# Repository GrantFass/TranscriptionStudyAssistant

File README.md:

# 24-Transcription-Study-Assistant

## Description
This project aims to create a tool that will assist in taking transcripts of courses and
breaking them down into pieces that can more easily be used for studying. This tool is 
intended to be utilized by all audiences but may be particularly beneficial for
neurodivergent students that face sensory overload during long lectures. 

This project is divided into three primary components.
1. Hardware
2. Web Software
3. Machine Learning

The hardware team is focusing on developing a video taking device for use with Microsoft
Teams, and other meeting software. This is meant to be an alternative to the [Meeting Owl 3](https://owllabs.com/products/meeting-owl-3?utm_source=adwords&utm_campaign=US_Branded&utm_medium=ppc&utm_term=meeting%20owl%203&hsa_kw=meeting%20owl%203&hsa_mt=e&hsa_tgt=kwd-1664191677785&hsa_src=g&hsa_ad=617179448370&hsa_ver=3&hsa_cam=1485487619&hsa_net=adwords&hsa_acc=2493962266&hsa_grp=78790216762&gclid=Cj0KCQiA_bieBhDSARIsADU4zLcaWRQWOvktF4fADjmooEcVXLYf4rbGnzq8EmovNgqnJcjop1JarCsaAsLBEALw_wcB).
The primary benefit that our device has over the meeting owl is cost. Our device aims to be
manufacturable as a proof of concept for under $200. This is much cheaper than the $1050
price tag the Meeting Owl 3 costs. Our device is meant to be an assistant for tracking
presenters in a classroom like environment for meetings.

The software team is focusing on developing a website that will support all the necessary
functions of our application, including our machine learning models. The website will be
designed so that video transcripts and other text based files can be uploaded to the server.
Then the server will allow you to modify and clean up the text, generate summaries of the
content, identify relevant topics, and possibly build study aids. An example study aid would
be question and answer flashcards.

The machine learning team is focusing on the models that allow us to summarize text and topics.
This is primarily done through transformers and Latent Dirichlet Allocation models.

## Badges
On some READMEs, you may see small images that convey metadata, such as whether or not all the tests are passing for the project. You can use Shields to add some to your README. Many services also have instructions for adding a badge.

## Visuals
Depending on what you are making, it can be a good idea to include screenshots or even a video (you'll frequently see GIFs rather than actual videos). Tools like ttygif can help, but check out Asciinema for a more sophisticated method.

## Automatic Installation
Running this project locally can be done through a few simple steps. 
The first step is to install `python 3.10.0`. Once that is done,
you should be able to install the project by running setup.py. Once this is
completed you can run the entire project through run.py

## Manual Installation
Running this project locally can be somewhat difficult as there are external requirements.
Assuming that the proper python version (as noted in the requirements section) is installed
it should be possible to install relevant python library files by running the command
`pip install -r requirements.txt` out of the software home directory.

This application uses the SpaCy library and its language kits. Unfortunately, these can not be
installed through pip. Instead, they must be installed through the command line.
There are three model sizes that must be installed to be able to run the software. These
models can be found from [SpaCy](https://spacy.io/models/en). Download using the following commands:
- `python -m spacy download en_core_web_sm`
- `python -m spacy download en_core_web_md`
- `python -m spacy download en_core_web_lg`

The SpaCy `en_core_web_trf` model is not required.

The step is installing MinIO. MinIO is an object store that can be downloaded [here](https://min.io/download#/windows).
Both the server, and the client, must be downloaded. If on Windows, this will give two files:
`minio.exe` and `mc.exe`. Place these two executeables in a folder that you can run things from.
In order to run the web backend you must launch a console out of the folder and run the command:
`minio server minio_data`. This starts the object store which allows for storing log files as
well as files that are uploaded to the program.

The next step is to set up users and buckets inside MinIO. Access the [MinIO web interface](http://127.0.0.1:9000/).
Log in with the default username `minioadmin` and default password `minioadmin`.
Next you should see a sidebar of options. Click on Administrator -> Identity -> Users ->
Create User. You should then create a user called `tsa-backend`. Give it a password you can
remember as well as read write access then save. Next navigate to Administrator -> Buckets.
We need to create a bucket called `tsa-backend-endpoint-logs` and another bucket called 
`tsa-backend-user-files`. We also need to create a bucket called `tsa-backend-account-info`. No parameters need to be changed on these buckets, so they can be saved right after setting their names.

After the MinIO setup is complete you need to add a .env file under the API folder.
This file should have the below format. You should fill in the password for the user you
created under the access key. If your object store is on another computer then set the
endpoint url to its location. If you decided to name your user something other than `tsa-backend`
above than change that as well.
```
AWS_ACCESS_KEY_ID = "tsa-backend"
AWS_SECRET_ACCESS_KEY = "minioadmin"
MINIO_URL = "http://localhost:9000"
ENDPOINT_LOG_PATH = "endpoint_log_file.json"
ENDPOINT_LOGS_BUCKET = 'tsa-backend-endpoint-logs'
USER_FILES_BUCKET = 'tsa-backend-user-files'
ACCOUNT_INFO_BUCKET = 'tsa-backend-account-info'
LOGIN_TRACKING_BUCKET = 'tsa-backend-login-tracking'
BACKEND_URL_FOR_TESTS = "http://localhost:8844"
```

If you are planning on testing the backend without the use of a frontend then you will
need to either use curl commands or install a tool to send http requests. Much of the
testing during development was done using [Postman](https://www.postman.com/downloads/).

## Running the Web Software
- Pull down the repo in Visual Studio Code.
- cd or navigate into the transcript-study-assistant folder using the terminal within VS Code.
- Type in "ng serve". The website should run at an address like http://localhost:4200/.
- If the website does not run, try running "npm install -g @angular/cli".
- Please contact Teresa with further questions. I'm happy to improve these instructions further.

## Requirements
- Python version 3.10

## Usage
Use examples liberally, and show the expected output if you can. It's helpful to have inline the smallest example of usage that you can demonstrate, while providing links to more sophisticated examples if they are too long to reasonably include in the README.

## Support
Tell people where they can go to for help. It can be any combination of an issue tracker, a chat room, an email address, etc.

## Roadmap
If you have ideas for releases in the future, it is a good idea to list them in the README.

## Contributing
State if you are open to contributions and what your requirements are for accepting them.

For people who want to make changes to your project, it's helpful to have some documentation on how to get started. Perhaps there is a script that they should run or some environment variables that they need to set. Make these steps explicit. These instructions could also be useful to your future self.

You can also document commands to lint the code or run tests. These steps help to ensure high code quality and reduce the likelihood that the changes inadvertently break something. Having instructions for running tests is especially helpful if it requires external setup, such as starting a Selenium server for testing in a browser.

## Authors and acknowledgment
Hardware Team:
- Angela Christie
- Alexander Karpov

Software Team:
- Teresa Toohill
- Grant Fass

Machine Learning Team:
- Nicholas Kaja
- Grant Fass

Advisor:
- Dr. Sohum Sohoni

Institution:
- Milwaukee School of Engineering 2022-2023

## License
For open source projects, say how it is licensed.

## Project status
If you have run out of energy or time for your project, put a note at the top of the README saying that development has slowed down or stopped completely. Someone may choose to fork your project or volunteer to step in as a maintainer or owner, allowing your project to keep going. You can also make an explicit request for maintainers.

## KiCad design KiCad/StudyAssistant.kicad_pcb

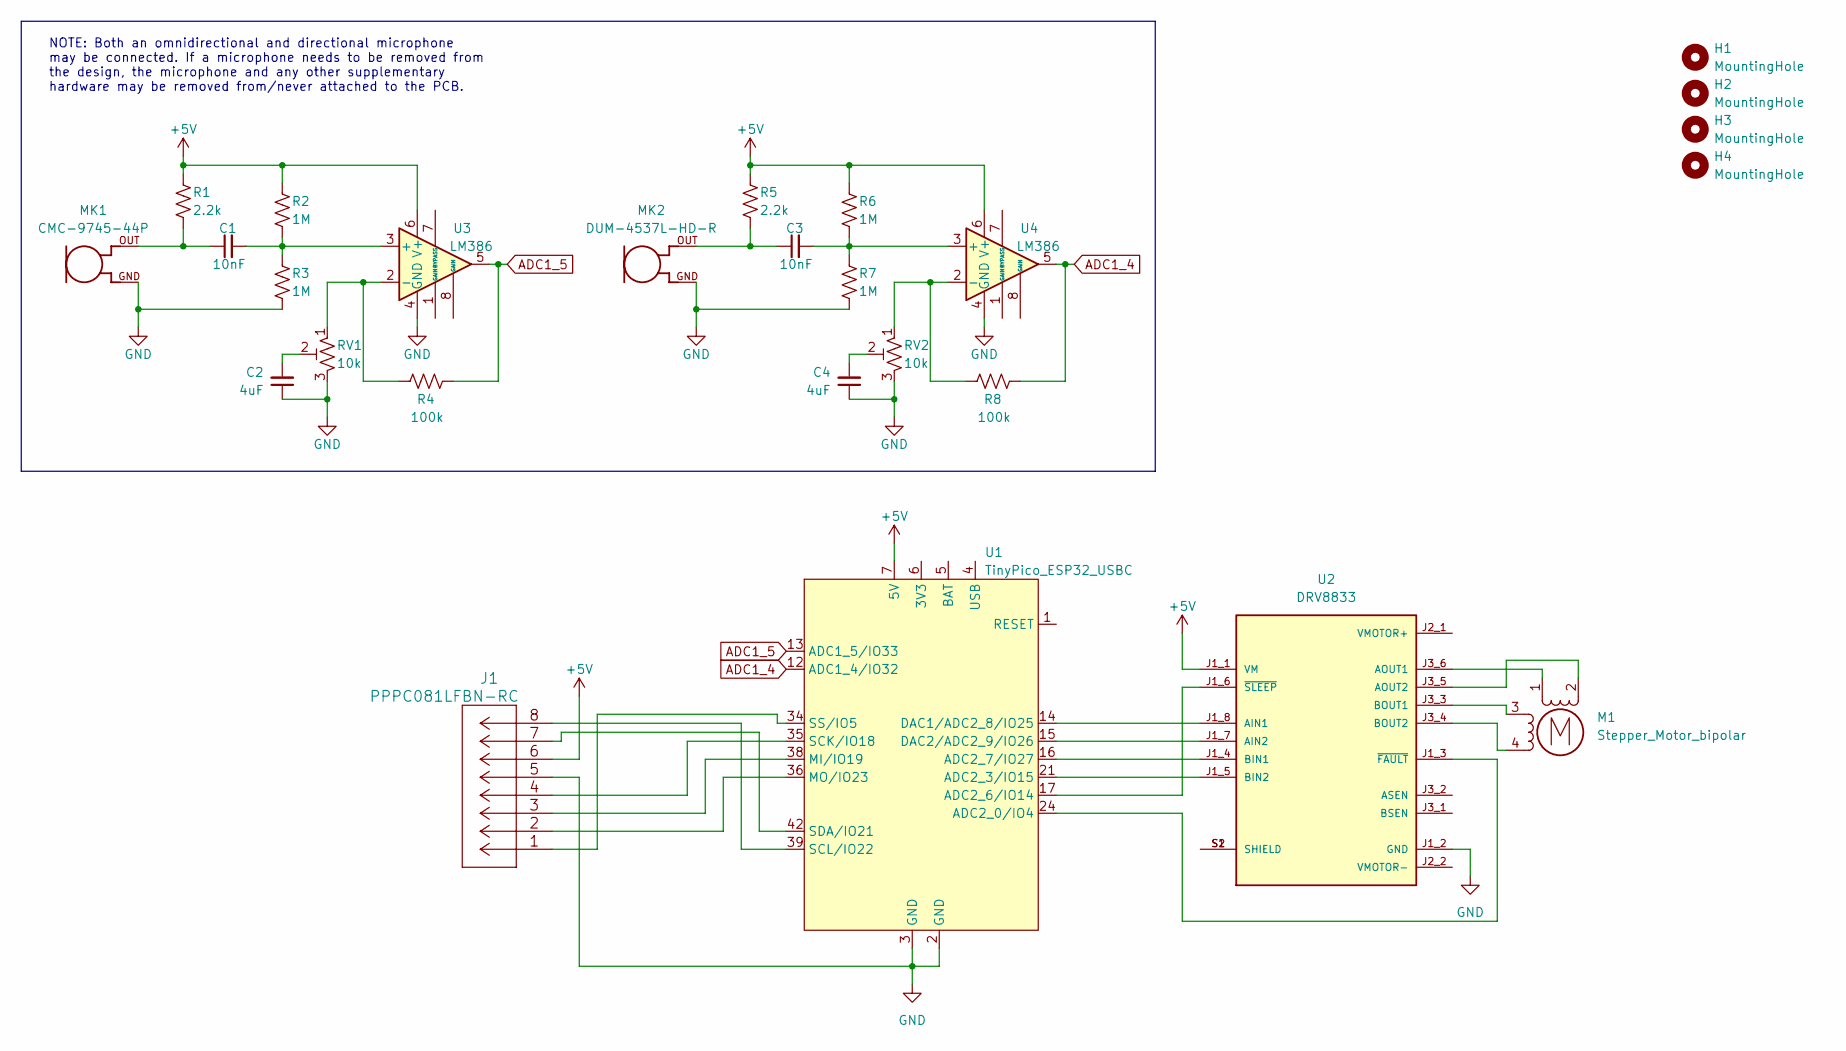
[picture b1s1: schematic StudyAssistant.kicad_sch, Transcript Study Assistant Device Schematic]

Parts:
C1, C3: 10nF; C_0805_2012Metric
C2, C4: 4uF; C_0805_2012Metric
H1, H2, H3, H4: MountingHole; MountingHole_3.2mm_M3
J1: PPPC081LFBN-RC
M1: Stepper_Motor_bipolar; PinHeader_1x04_P2.54mm_Vertical
MK1: CMC-9745-44P; THT-CUI-CMC-9745-44P; PARTREV 1
MK2: DUM-4537L-HD-R; THT-DUM-4537L-HD-R; PARTREV 1
R1, R5: 2.2k; R_0805_2012Metric
R2, R3, R6, R7: 1M; R_0805_2012Metric
R4, R8: 100k; R_0805_2012Metric
RV1, RV2: 10k; TRIM_COM-09806
U1: TinyPico_ESP32_USBC; TinyPICO-ESP32-DevBoard
U2: DRV8833; PARTREV 2020-11-20
U3, U4: LM386; LM386_M1_NOPB

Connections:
+5V: J1.6, R1.1, R2.1, R5.1, R6.1, U1.7 (5V), U2.J1_1 (VM), U3.6 (V+), U4.6 (V+)
ADC1_4: R8.2, U1.12 (ADC1_4/IO32), U4.5
ADC1_5: R4.2, U1.13 (ADC1_5/IO33), U3.5
GND: C2.1, C4.1, J1.5, MK1.GND, MK2.GND, R3.2, R7.2, RV1.3, RV2.3, U1.2 (GND), U1.3 (GND), U2.J1_2 (GND), U3.4 (GND), U4.4 (GND)
unnamed: C3.2, R6.2, R7.1, U4.3 (+)
unnamed: J1.1, U1.34 (SS/IO5)
unnamed: J1.2, U1.36 (MO/IO23)
unnamed: J1.3, U1.38 (MI/IO19)
unnamed: J1.4, U1.35 (SCK/IO18)
unnamed: J1.7, U1.42 (SDA/IO21)
unnamed: J1.8, U1.39 (SCL/IO22)
unnamed: C1.1, MK1.OUT, R1.2
unnamed: C3.1, MK2.OUT, R5.2
unnamed: C2.2, RV1.2
unnamed: R8.1, RV2.1, U4.2 (-)
unnamed: C4.2, RV2.2
unnamed: U1.14 (DAC1/ADC2_8/IO25), U2.J1_8 (AIN1)
unnamed: U1.15 (DAC2/ADC2_9/IO26), U2.J1_7 (AIN2)
unnamed: U1.16 (ADC2_7/IO27), U2.J1_4 (BIN1)
unnamed: U1.17 (ADC2_6/IO14), U2.J1_6 (~SLEEP)
unnamed: U1.21 (ADC2_3/IO15), U2.J1_5 (BIN2)
unnamed: U1.24 (ADC2_0/IO4), U2.J1_3 (~FAULT)
unnamed: M1.3, U2.J3_3 (BOUT1)
unnamed: M1.4, U2.J3_4 (BOUT2)
unnamed: M1.2 (-), U2.J3_5 (AOUT2)
unnamed: M1.1, U2.J3_6 (AOUT1)
unnamed: R4.1, RV1.1, U3.2 (-)
unnamed: C1.2, R2.2, R3.1, U3.3 (+)

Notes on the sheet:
NOTE: Both an omnidirectional and directional microphone may be connected. If a microphone needs to be removed from the design, the microphone and any other supplementary hardware may be removed from/never attached to the PCB.

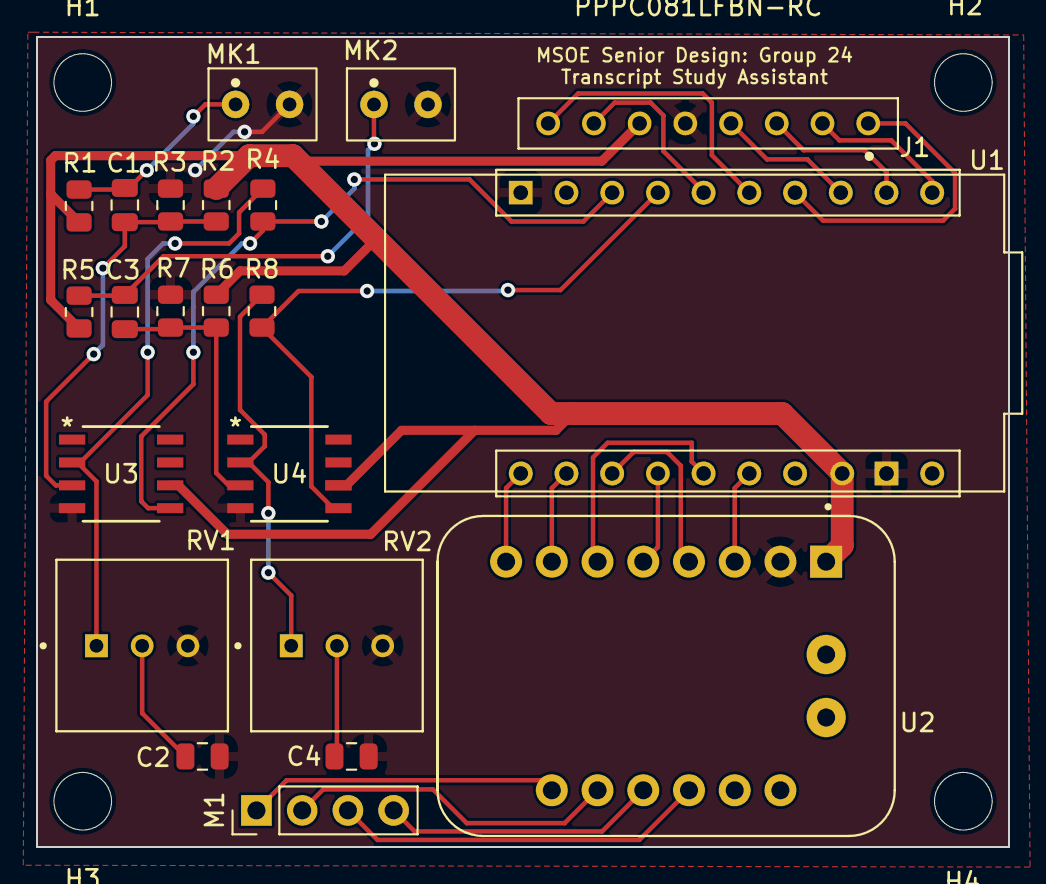
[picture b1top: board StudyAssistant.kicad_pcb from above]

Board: 2 copper layers, 54.0 x 45.0 mm, 26 parts (0 on the bottom side), 28 nets.

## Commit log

2023-06-14 Upload GitIgnore
2023-06-14 Add transcription Study Assistant
2023-06-14 Add the wiki in
2023-06-14 Add website

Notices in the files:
parts and their libraries:
Copyright 2021 Accelerated Designs. All rights reserved.
